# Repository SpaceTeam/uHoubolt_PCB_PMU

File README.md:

# µHoubolt Power Management Unit (PMU) Hardware

## Features
- Altimeter capability (barometer, IMU, 2x Low Side Fet)
- 2x Low Side Fet for camera
- 1x Optocoupler for payload enable
- 2x LiIon Charger
- Flash for data logging
- 2x CAN FD

## Known Issues
- CAN Rx and Tx are swapped on CAN1 and CAN2
- No Battery Voltage Sense
- No Pyro Voltage Sense
- Same Connector for 12V and 24V
- No direct hardware arming for primary altimax
- Supply Current Sense is connected to the wrong pin
- Layout: Battery connector is hard to disconnect because it's next to the mounting hole (threaded rod)
- When powering cameras from pyro voltage, their initial current draw is large enough to trigger the overcurrent protection --> all supplied devices might get power cycled when safety pin is pulled (especially bad for ECU, might cause igniters to fire, see ECU known issues)

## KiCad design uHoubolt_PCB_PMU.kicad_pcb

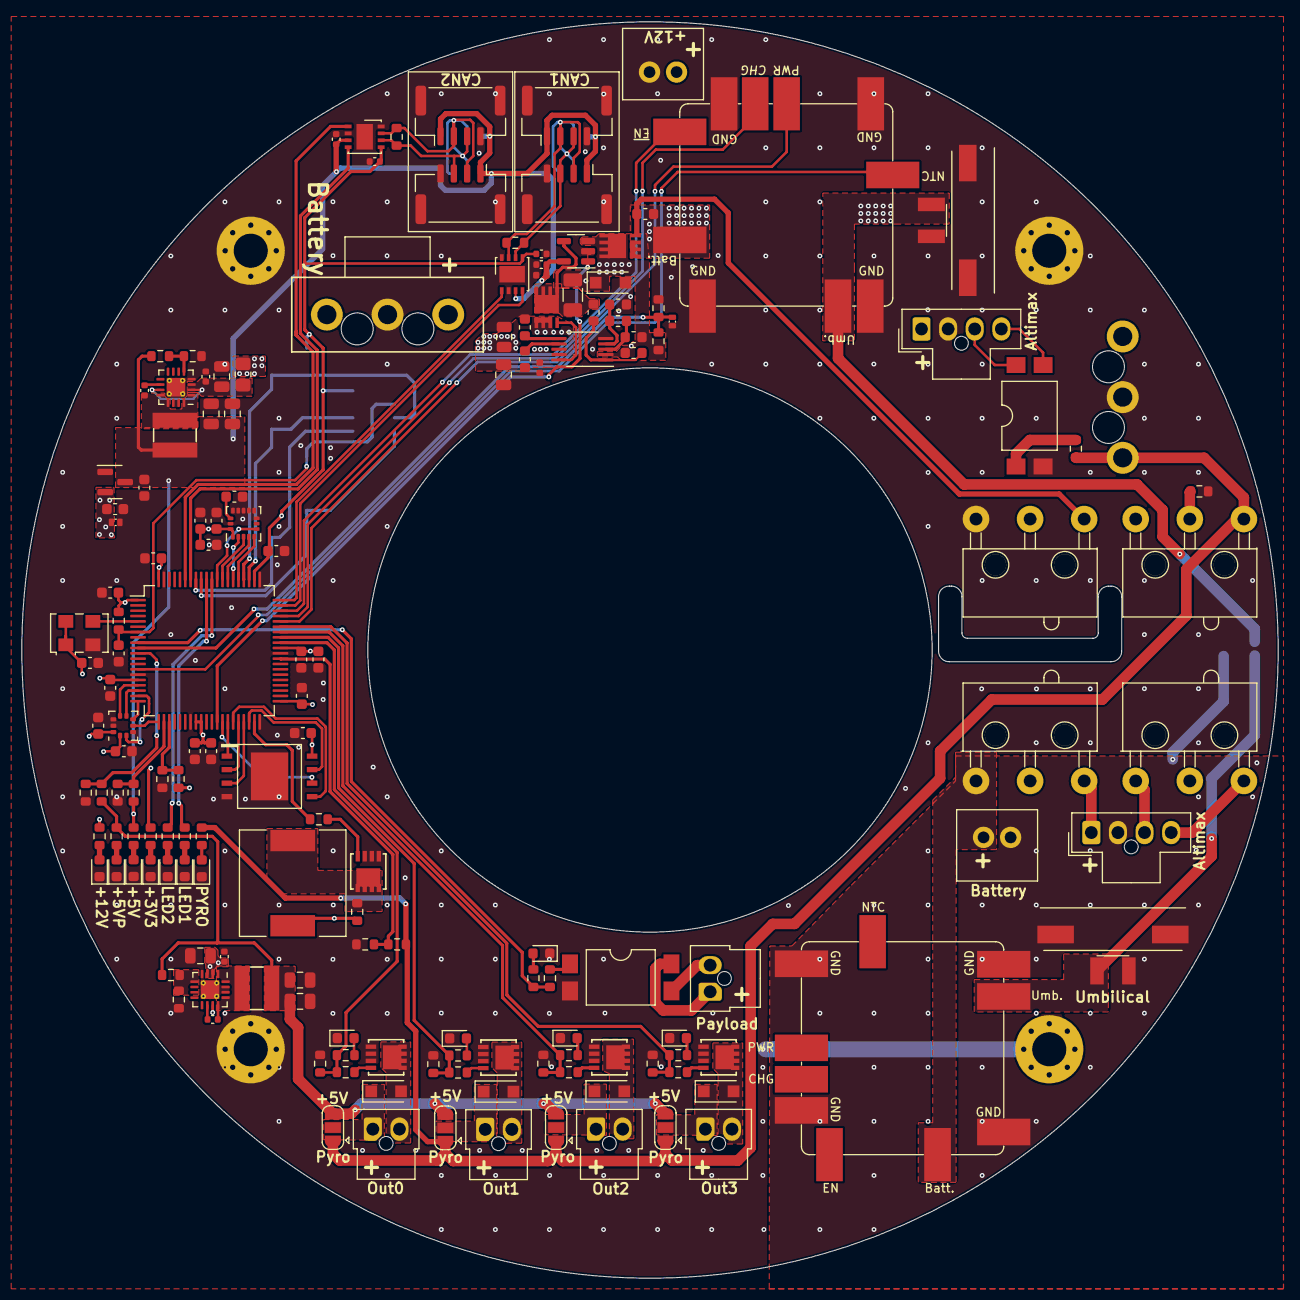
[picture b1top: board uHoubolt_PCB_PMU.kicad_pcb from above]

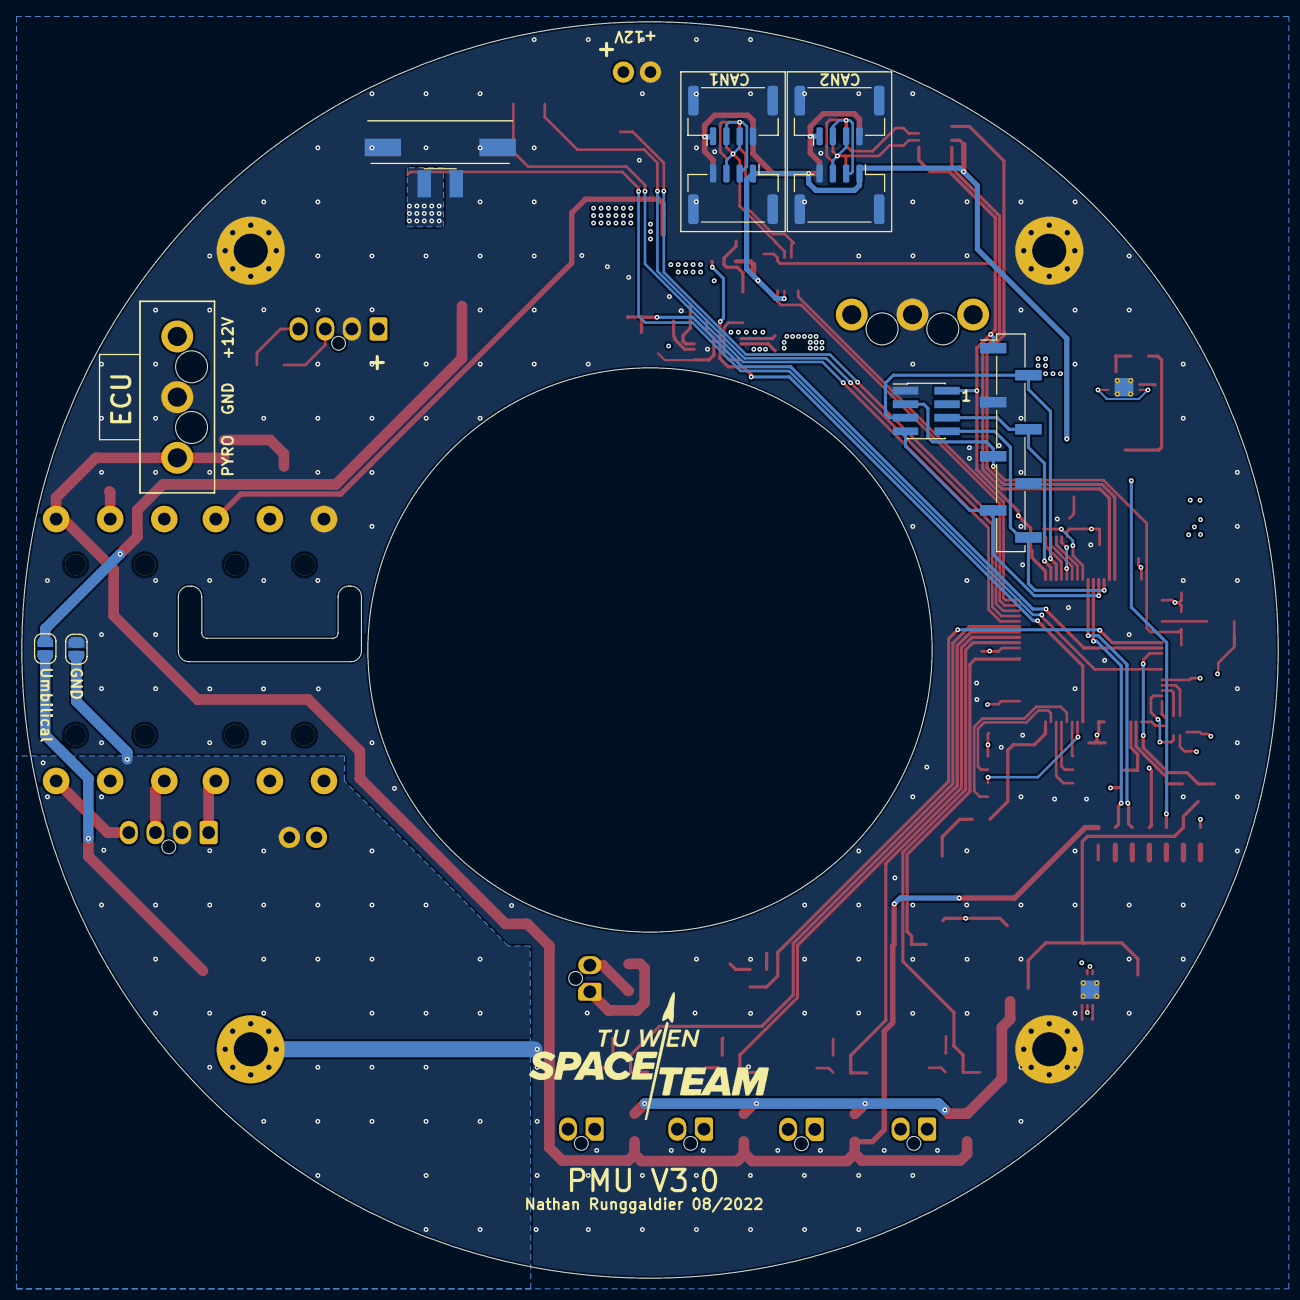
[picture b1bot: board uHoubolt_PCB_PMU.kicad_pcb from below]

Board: 4 copper layers, 118.0 x 118.0 mm, 174 parts (11 on the bottom side), 112 nets.

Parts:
C1: 470n; C_0603_1608Metric
C2, C20, C21, C23, C25, C26, C27, C28, C29, C30, C35, C40, C41, C42: 100n; C_0603_1608Metric
C3, C6, C15, C19, C32, C33, C37, C38, C45, C46: 100n; C_0402_1005Metric
C4, C5, C16, C17, C43, C44, C47, C48: 22u; C_0805_2012Metric
C22, C24, C31, C34, C36: 2u2; C_0603_1608Metric
C39: 10n; C_0603_1608Metric
D1: 30V; D_SOD-123F
D2: VIN; LED_0603_1608Metric
D3: Pyro; LED_0603_1608Metric
D4, D8: TVS 3V3; SOD882D
D7, D16: 5V; LED_0603_1608Metric
D9: 3V3; LED_0603_1608Metric
D10, D12, D14, D17: OUT; LED_0603_1608Metric
D11, D13, D15, D18: Shottky; D_SOD-123F
D25: Payload; LED_0603_1608Metric
F1: Fuse_Small; R_0805_2012Metric_Pad1.20x1.40mm_HandSolder
G1: SpaceTeam_LOGO; ST_Logo_new
H1, H2, H3, H4: M3; MountingHole_3.2mm_M3_Pad_Via
J1, J7: Conn_01x04; Molex_Nano-Fit_105309-xx04_1x04_P2.50mm_Vertical
J2: Battery; Molex_MegaFit_1x03_Vertical
J3: Power; Molex_MegaFit_1x03_Vertical
J4: BatteryAltimax; Molex_SL_1x2_Vertical
J5: Umbilical1; Molex_MicroFit_2Pin_Vertical
J9: Debug; PinHeader_1x08_P2.54mm_Vertical_SMD_Pin1Left
J10: Debug; PinHeader_2x04_P1.27mm_Vertical_SMD
J12, J14, J16, J18: CAN1; JST_GH_BM04B-GHS-TBT_1x04-1MP_P1.25mm_Vertical
J13, J15, J17, J19: CAN2; JST_GH_BM04B-GHS-TBT_1x04-1MP_P1.25mm_Vertical
J20, J21, J22, J24: Output; Molex_Nano-Fit_105309-xx02_1x02_P2.50mm_Vertical
J23: Payload; Molex_Nano-Fit_105309-xx02_1x02_P2.50mm_Vertical
J25: RCU; Molex_SL_1x2_Vertical
J27, J28: Umbilical0; Molex_MicroFit_2Pin_Vertical
JP2, JP3: Jumper_2_Open; SolderJumper-2_P1.3mm_Open_RoundedPad1.0x1.5mm
JP4, JP5, JP6, JP7: Jumper_3_Open; SolderJumper-3_P1.3mm_Open_RoundedPad1.0x1.5mm
L1, L3: 4.7u; SRN4018TA-4R7M
LED1, LED2: LED_Small_Filled; LED_0603_1608Metric
LS1: Speaker; Piezo_Buzzer
Q1: BSZ0905PNSATMA1; PG_TSDSON-8
Q2: BSZ0902NSATMA1; PG_TSDSON-8
Q3, Q4, Q5, Q6, Q7: SISA88DN or similar; PowerPAK_1212-8
R1, R8, R14, R20, R21, R25, R26, R33, R36, R39, R41, R46, R47, R48: 10k; R_0603_1608Metric
R2, R3, R4, R17, R18, R22, R31, R43, R44: R; R_0603_1608Metric
R5: NP; R_0603_1608Metric
R6: 2m; R_1206_3216Metric
R7: 0R; R_0603_1608Metric
R9: 47k; R_0603_1608Metric
R10, R16, R19, R23, R45: 1k; R_0603_1608Metric
R11, R12, R15, R28, R29, R30, R32, R34, R35, R37, R38, R40, R42, R49, R56: 120; R_0603_1608Metric
R13, R24, R27: 56k; R_0603_1608Metric
SW1: Power_1; D2F_A
SW2: Power_2; D2F_A1
SW3: Pyro_1; D2F_A
SW4: Pyro_2; D2F_A1
U1: LM5069; VSSOP-10_3x3mm_P0.5mm
U2: LMP8640 F; SOT-23-5
U3, U13: TS30041; QFN-16-1EP_3x3mm_P0.5mm_EP1.75x1.75mm_ThermalVias
U4, U14: LiIon_Charger; LiIon_Charger_Footprint
U5: STM32G491MET6-LQFP80; LQFP-80_12x12mm_P0.5mm
U6: W25Q256JV; WSON-8-8x6mm
U7: MCP1700-3302E; SOT-23
U8, U9: MCP2562FDx-x_MF; DFN-8-1EP_3x3mm_P0.65mm_EP1.55x2.4mm
U10: ICM-20602; LGA-16_3x3mm_P0.5mm_LayoutBorder3x5y
U11: LPS25HB; ST_HLGA-10_2.5x2.5mm_P0.6mm_LayoutBorder3x2y
U12, U15: SFH617A-1X007T; SMDIP-4_W9.53mm_Clearance8mm
X1: TXC-7C; Oscillator_SMD_TXC_7C-4Pin_5.0x3.2mm

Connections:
+3V3: C2.1, C21.2, C22.2, C23.2, C24.2, C25.2, C26.2, C27.1, C28.2, C29.2, C30.2, C32.1, C33.1, C34.2, C35.2, C36.1, C39.1, C41.2, C42.1, D8.1 (K), J9.1, J10.2, R8.1, R30.1, U5.1 (VBAT), U5.16 (VDD), U5.28 (VREF+), U5.29 (VDDA), U5.41 (VDD), U5.51 (VDD), U5.62 (VDD), U5.80 (VDD), U6.8 (VCC), U7.2 (VO), U8.5 (Vio), U9.5 (Vio), U10.1 (VDDIO), U10.16 (VDD), U11.1 (VDDio), U11.10 (VDD), X1.1 (EN), X1.4 (Vdd)
+5V: C19.1, C31.1, C37.1, C38.1, C47.2, C48.2, J12.1, J13.1, J14.1, J15.1, J16.1, J17.1, J18.1, J19.1, L3.2, R43.2, R45.1, R46.1, U2.5 (V+), U7.3 (VI), U8.3 (VDD), U9.3 (VDD)
+5VP: C16.2, C17.2, JP4.3 (B), JP5.3 (B), JP6.3 (B), JP7.3 (B), L1.2, R17.2, R19.1, R20.1
+12V: C3.1, C4.1, C5.2, C6.1, C43.1, J3.1, J7.1, J25.1, LS1.1, Q2.1 (S), R10.1, R13.1, R16.1, SW3.1 (A), U1.9 (OUT), U3.2 (VCC), U3.3 (VCC), U3.11 (VCC)
+BATT: J2.1, Q1.1 (S), R1.1, U4.2 (Battery)
/5V/Input: C44.2, C45.1, F1.2, U13.2 (VCC), U13.3 (VCC), U13.11 (VCC)
/5VP_Sense: R20.2, R21.1, U5.11 (PC3)
/5V_Sense: R46.2, R47.1, U5.22 (PC4)
/12V_Sense: R13.2, R14.1, U5.23 (PC5)
/BARO_INT: U5.17 (PA3), U11.7 (INT_DRDY)
/BARO_SPI1_MISO: U5.20 (PA6), U11.5 (SA0/MISO)
/BARO_SPI1_MOSI: U5.21 (PA7), U11.4 (SDA/MOSI)
/BARO_SPI1_NSS: U5.18 (PA4), U11.6 (~CS)
/BARO_SPI1_SCK: U5.19 (PA5), U11.2 (SCL/SCLK)
/Battery_Sense: D4.1 (K), R26.1, R27.2, U5.10 (PC2)
/CAN1_H: J12.2, J14.2, J16.2, J18.2, R28.1, U8.7 (CANH)
/CAN1_L: J12.3, J14.3, J16.3, J18.3, R28.2, U8.6 (CANL)
/CAN1_RX: U5.59 (PA11), U8.4 (RXD)
/CAN1_TX: U5.60 (PA12), U8.1 (TXD)
/CAN2_H: J13.2, J15.2, J17.2, J19.2, R29.1, U9.7 (CANH)
/CAN2_L: J13.3, J15.3, J17.3, J19.3, R29.2, U9.6 (CANL)
/CAN2_RX: U5.74 (PB5), U9.4 (RXD)
/CAN2_TX: U5.75 (PB6), U9.1 (TXD)
/GND_Altimax: J1.2, J4.2, J5.2, J5.MP (MountPin), JP3.2 (B), U14.1 (GND), U14.4 (GND), U14.7 (GND), U14.9 (GND)
/HSE_CLK: U5.5 (PF0-OSC_IN), X1.3 (OUT)
/IMU_INT: U5.69 (PD0), U10.6 (INT)
/IMU_NSS: U5.65 (PA15), U10.5 (~CS)
/IMU_SPI3_MISO: U5.67 (PC11), U10.4 (SAO/SD0)
/IMU_SPI3_MOSI: U5.68 (PC12), U10.3 (SDA/SDI)
/IMU_SPI3_SCK: U5.66 (PC10), U10.2 (SCL/SPC)
/LED1: R11.1, U5.71 (PD2)
/LED2: R12.1, U5.70 (PD1)
/NRST: C20.1, J9.5, J10.3, R8.2, U5.7 (PG10-NRST)
/NTC: U4.8 (NTC), U5.14 (PA2)
/Out0: R32.1, R33.2, R34.1, U5.52 (PC6)
/Out1: R35.1, R36.2, R37.1, U5.53 (PC7)
/Out2: R38.1, R39.2, R40.1, U5.54 (PC8)
/Out3: R42.1, R48.2, R49.1, U5.55 (PC9)
/Payload: R31.1, R56.1, U5.9 (PC1)
/Pyro_Sense: R24.2, R25.1, U5.49 (PD10)
/QSPI1_BK1_IO0: U5.35 (PE12), U6.5 (DI(IO0))
/QSPI1_BK1_IO1: U5.36 (PE13), U6.2 (DO(IO1))
/QSPI1_BK1_IO2: U5.37 (PE14), U6.3 (~WP(IO2))
/QSPI1_BK1_IO3: U5.38 (PE15), U6.7 (~RESET(IO3))
/QSPI1_BK1_NCS: U5.34 (PE11), U6.1 (~CS)
/QSPI1_CLK: U5.33 (PE10), U6.6 (CLK)
/SUPPLY_CURRENT_SENSE: U2.1, U5.32 (PE9)
/SWCLK: J9.2, J10.5, U5.64 (PA14)
/SWDIO: J9.4, J10.6, U5.63 (PA13)
/Speaker: R15.1, U5.39 (PB10)
/UART_RX: J9.8, J10.8, U5.73 (PB4)
/UART_TX: J9.7, J10.7, U5.72 (PB3)
/Vcharge: J27.1, J28.1, JP2.1 (A), U4.10 (Umb.)
/Vcharge1: J5.1, JP2.2 (B), U14.10 (Umb.)
/Vin: D1.1 (A1), F1.1, Q1.3 (D), R2.1, R5.1, R6.1, R27.1, U1.2 (VIN), U2.3 (+)
/~ACOK: U4.6 (ACOK), U5.56 (PA8)
/~CHGOK: U4.5 (CHGOK), U5.57 (PA9)
/~EN: U4.3 (EN), U5.58 (PA10)
GND: C1.2, C2.2, C3.2, C4.2, C5.1, C6.2, C16.1, C17.1, C19.2, C20.2, C21.1, C22.1, C23.1, C24.1, C25.1, C26.1, C27.2, C28.1, C29.1, C30.1, C31.2, C32.2, C33.2, C34.1, C35.1, C36.2, C37.2, C38.2, C39.2, C40.2, C41.1, C42.2, C43.2, C44.1, C45.2, C47.1, C48.1, D1.2 (A2), D2.1 (K), D3.1 (K), D4.2 (A), D7.1 (K), D8.2 (A), D9.1 (K), D10.1 (K), D12.1 (K), D14.1 (K), D16.1 (K), D17.1 (K), D25.1 (K), H1.1, H2.1, H3.1, H4.1, J2.2, J3.2, J7.2, J9.3, J10.1, J12.4, J12.MP (MountPin), J13.4, J13.MP (MountPin), J14.4, J14.MP (MountPin), J15.4, J15.MP (MountPin), J16.4, J16.MP (MountPin), J17.4, J17.MP (MountPin), J18.4, J18.MP (MountPin), J19.4, J19.MP (MountPin), J25.2, J27.2, J27.MP (MountPin), J28.2, J28.MP (MountPin), JP3.1 (A), LED1.1 (K), LED2.1 (K), Q3.3 (S), Q4.3 (S), Q5.3 (S), Q6.3 (S), Q7.3 (S), R4.2, R9.2, R14.2, R18.2, R21.2, R25.2, R26.2, R33.1, R36.1, R39.1, R41.2, R44.2, R47.2, R48.1, SW1.1 (A), U1.5 (GND), U2.2 (GND), U3.4 (GND), U3.14 (PGND), U3.15 (PGND), U3.17 (PAD), U4.1 (GND), U4.4 (GND), U4.7 (GND), U4.9 (GND), U5.15 (VSS), U5.27 (VSSA), U5.40 (VSS), U5.50 (VSS), U5.61 (VSS), U5.79 (VSS), U6.4 (GND), U6.9 (PAD), U7.1 (GND), U8.2 (VSS), U8.8 (STBY), U8.9 (PAD), U9.2 (VSS), U9.8 (STBY), U9.9 (PAD), U10.8 (FSYNC), U10.9 (GND), U10.10 (GND), U10.11 (GND), U10.12 (GND), U10.13 (GND), U10.15 (GND), U11.3 (GND), U11.8 (GND), U11.9 (GND), U12.2, U13.4 (GND), U13.14 (PGND), U13.15 (PGND), U13.17 (PAD), U15.2, X1.2 (GND)
unnamed: C1.1, U1.6 (TIMER)
unnamed: C15.1, L1.1, U3.1 (VSW), U3.12 (VSW), U3.13 (VSW), U3.16 (VSW)
unnamed: C15.2, U3.10 (BST)
unnamed: C40.1, U10.14 (REGOUT)
unnamed: C46.1, L3.1, U13.1 (VSW), U13.12 (VSW), U13.13 (VSW), U13.16 (VSW)
unnamed: C46.2, U13.10 (BST)
unnamed: D2.2 (A), R10.2
unnamed: D3.2 (A), R23.2
unnamed: D7.2 (A), R19.2
unnamed: D9.2 (A), R30.2
unnamed: D10.2 (A), R32.2
unnamed: D11.1 (K), J20.1, JP4.2 (C)
unnamed: D11.2 (A), J20.2, Q4.2 (D)
unnamed: D12.2 (A), R35.2
unnamed: D13.1 (K), J21.1, JP5.2 (C)
unnamed: D13.2 (A), J21.2, Q5.2 (D)
unnamed: D14.2 (A), R38.2
unnamed: D15.1 (K), J22.1, JP6.2 (C)
unnamed: D15.2 (A), J22.2, Q6.2 (D)
unnamed: D16.2 (A), R45.2
unnamed: D17.2 (A), R42.2
unnamed: D18.1 (K), J24.1, JP7.2 (C)
unnamed: D18.2 (A), J24.2, Q7.2 (D)
unnamed: D25.2 (A), R56.2
unnamed: J1.1, SW2.2 (B)
unnamed: J1.3, SW4.1 (A)
unnamed: J1.4, SW4.2 (B)
unnamed: J4.1, SW2.1 (A), U14.2 (Battery)
unnamed: J7.3, U15.4
unnamed: J7.4, U15.3
unnamed: J23.1, U12.4
unnamed: J23.2, U12.3
unnamed: LED1.2 (A), R11.2
unnamed: LED2.2 (A), R12.2
unnamed: LS1.2, Q3.2 (D), R16.2
unnamed: Q1.2 (G), R1.2, SW1.2 (B)
unnamed: Q2.2 (G), U1.10 (GATE)
unnamed: Q2.3 (D), R6.2, R7.2, U2.4 (-)
unnamed: Q3.1 (G), R15.2
unnamed: Q4.1 (G), R34.2
unnamed: Q5.1 (G), R37.2
unnamed: Q6.1 (G), R40.2
unnamed: Q7.1 (G), R49.2
unnamed: R2.2, R3.1, U1.3 (UVLO)
unnamed: R3.2, R4.1, U1.4 (OVLO)
unnamed: R5.2, R7.1, U1.1 (SENSE)
unnamed: R9.1, U1.7 (PWR)
unnamed: R17.1, R18.1, U3.5 (FB)
unnamed: R22.2, U15.1
unnamed: R31.2, U12.1
unnamed: R41.1, SW3.3 (C)
unnamed: R43.1, R44.1, U13.5 (FB)
PYRO: J3.3, JP4.1 (A), JP5.1 (A), JP6.1 (A), JP7.1 (A), R22.1, R23.1, R24.1, SW3.2 (B)

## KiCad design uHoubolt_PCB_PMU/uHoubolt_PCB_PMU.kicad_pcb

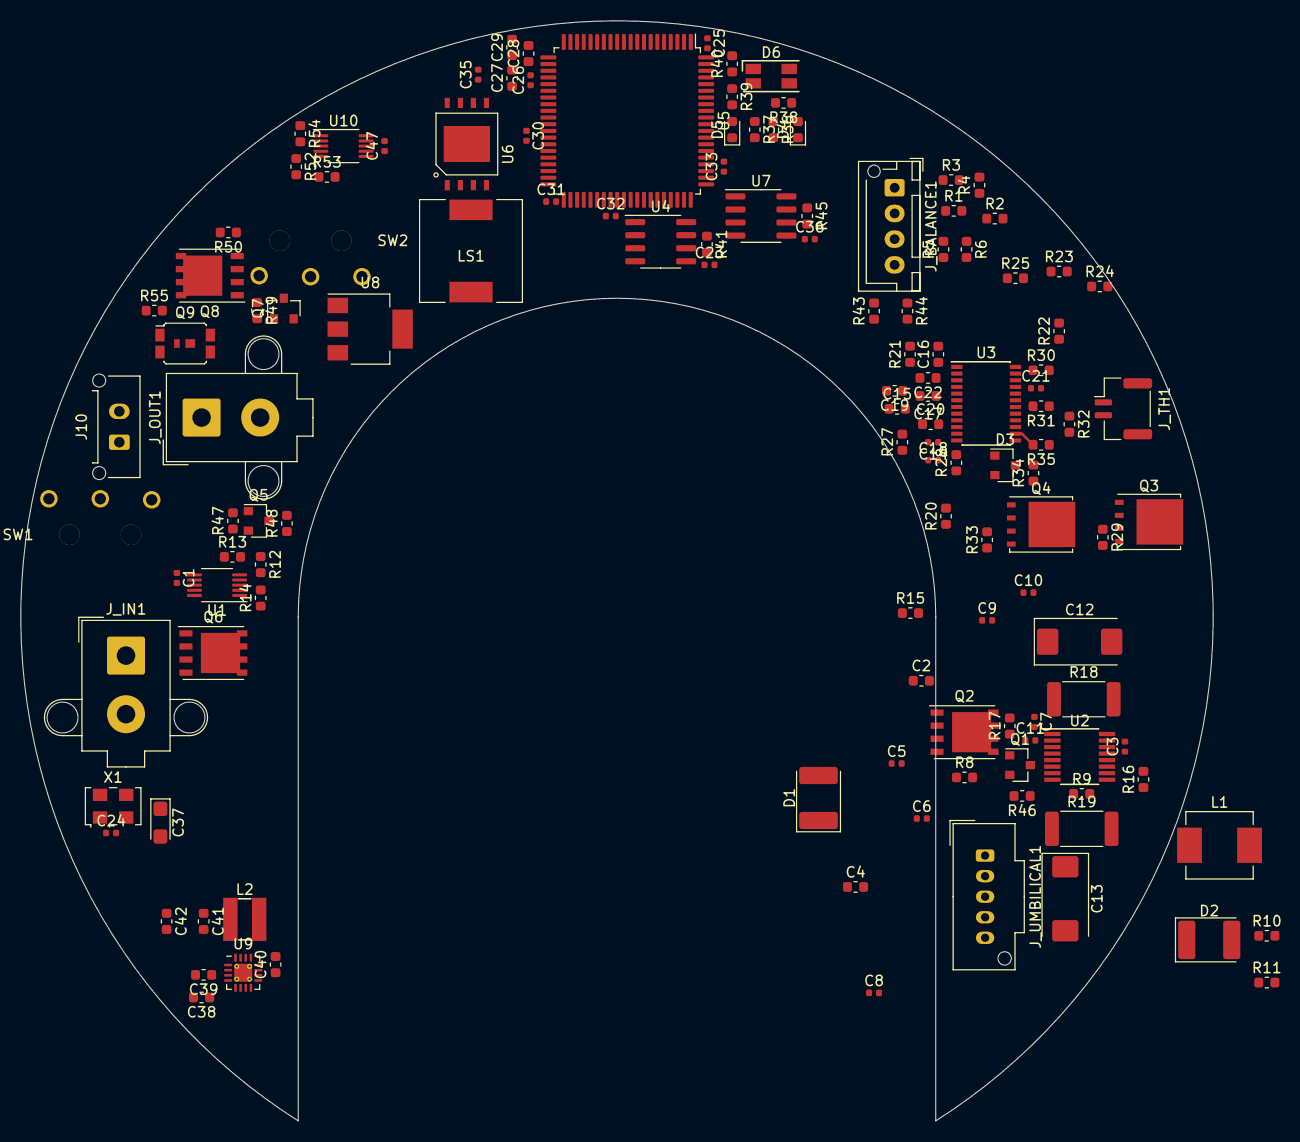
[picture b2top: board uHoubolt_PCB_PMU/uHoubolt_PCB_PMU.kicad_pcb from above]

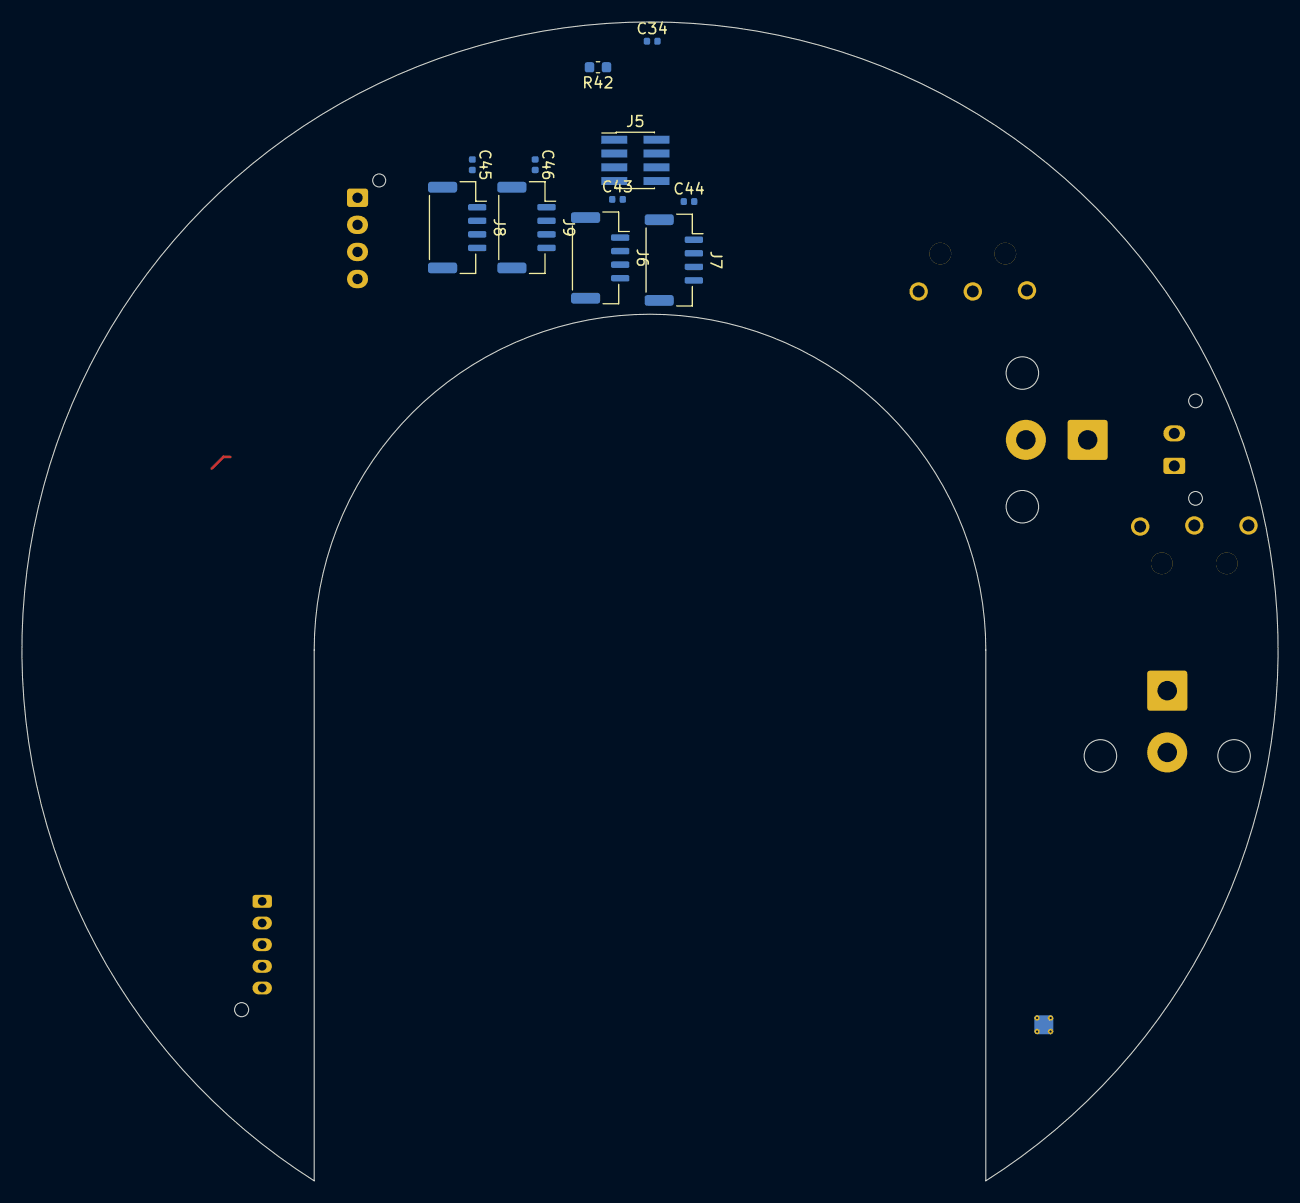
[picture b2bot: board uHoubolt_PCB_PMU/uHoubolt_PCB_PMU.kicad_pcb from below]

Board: 4 copper layers, 116.0 x 107.0 mm, 141 parts (11 on the bottom side), 100 nets.

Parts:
C1, C10, C14, C18, C21, C23, C24, C25, C30, C31, C32, C33, C34, C35, C36, C43, C44, C45, C46, C47: 100n; C_0402_1005Metric
C2, C15, C16, C17, C19, C20, C22, C27, C28, C29: 1u; C_0603_1608Metric
C3, C5: 220n; C_0402_1005Metric
C4: 2.2u; C_0603_1608Metric
C6: 1n; C_0402_1005Metric
C7, C11, C26: 10n; C_0402_1005Metric
C8, C9: 47n; C_0402_1005Metric
C12: 47u; CP_EIA-7343-43_Kemet-X
C13: 68uF; CP_EIA-7343-31_Kemet-D
C37: 22u; CP_EIA-3216-18_Kemet-A
C38: 10µ; C_0603_1608Metric
C39, C40: 100n; C_0603_1608Metric
C41, C42: 22µ; C_0603_1608Metric
D1, D2: D_Schottky; D_2114_3652Metric
D3: D_Zener; D_SOT-23_ANK
D4, D5: LED; LED_0603_1608Metric
D6: LED_RGBC; LED_RGB_1210
J5: Conn_02x04_Odd_Even; PinHeader_2x04_P1.27mm_Vertical_SMD
J6, J7, J8, J9: Conn_01x04_MountingPin; JST_GH_SM04B-GHS-TB_1x04-1MP_P1.25mm_Horizontal
J10: Conn_01x02; Molex_Micro-Fit_3.0_43650-0215_1x02_P3.00mm_Vertical
J_BALANCE1: Conn_01x04; JST_XH_B4B-XH-AM_1x04_P2.50mm_Vertical
J_IN1: Conn_01x02; Molex_Mega-Fit_76829-0002_2x01_P5.70mm_Vertical
J_OUT1: Conn_01x02; Molex_Mega-Fit_76829-0002_2x01_P5.70mm_Vertical
J_TH1: Conn_01x02_MP; JST_GH_BM02B-GHS-TBT_1x02-1MP_P1.25mm_Vertical
J_UMBILICAL1: Conn_01x04_MountingPin; Molex_MicroClasp_55932-0510_1x05_P2.00mm_Vertical
L1: 10uH; L_Vishay_IHLP-2525
L2: 4µ7; SRN4018TA-4R7M
LS1: Speaker_Crystal; Piezo_Buzzer
Q1: ZXMN3F30FH; SOT-23
Q2, Q6, Q8: Si7141DP; PowerPAK_SO-8_Single
Q3, Q4: CSD17303Q5; TDSON-8-1
Q5, Q7: MMBT3904; SOT-23
Q9: BSF030NE2LQ; DirectFET_SQ
R1: 3k; R_0603_1608Metric
R2: 1k5; R_0603_1608Metric
R3: 500; R_0603_1608Metric
R4, R6, R21, R47, R48, R49, R50, R55: 1k; R_0603_1608Metric
R5, R15, R30, R31, R42, R43, R46: 10k; R_0603_1608Metric
R8: 200; R_0603_1608Metric
R9, R10, R11, R32: 100k; R_0603_1608Metric
R12, R13, R14, R52, R53, R54: 2.7k; R_0603_1608Metric
R16, R17: 4.7; R_0603_1608Metric
R18: 0.033; R_2512_6332Metric
R19: 0.068; R_2512_6332Metric
R20, R22, R23, R24: 134; R_0603_1608Metric
R25, R27: 100; R_0603_1608Metric
R28: 4.5k; R_0603_1608Metric
R29, R33: 1M; R_0603_1608Metric
R34: 3.3M; R_0603_1608Metric
R35: 470k; R_0603_1608Metric
R36, R37, R38, R39, R40, R41, R45: 120; R_0603_1608Metric
R44: 2k; R_0603_1608Metric
SW1, SW2: SW_Push_SPDT; MicroSwitch
U1, U10: INA226; VSSOP-10_3x3mm_P0.5mm
U2: MAX1873SEEE; QSOP-16_3.9x4.9mm_P0.635mm
U3: BQ77915; TSSOP-24_4.4x7.8mm_P0.65mm
U4, U7: MCP2562FDT-H_SN; SOIC-8_3.9x4.9mm_P1.27mm
U5: STM32G491MET6-LQFP80; LQFP-80_14x14mm_P0.65mm
U6: W25Q256JV; WSON-8-8x6mm
U8: MCP1826S; SOT-223-3_TabPin2
U9: TS30041-M050QFNR; QFN-16-1EP_3x3mm_P0.5mm_EP1.75x1.75mm_ThermalVias
X1: TXC-7C; Oscillator_SMD_TXC_7C-4Pin_5.0x3.2mm

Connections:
+3V3: C1.1, C23.1, C24.1, C25.1, C26.2, C27.2, C28.2, C29.2, C30.2, C31.2, C32.2, C33.2, C34.2, C35.1, C36.1, C37.2, C47.1, J5.2, R12.1, R13.1, R14.1, R42.2, R52.1, R53.1, R54.1, U1.6, U4.5, U5.16, U5.41, U5.51, U5.62, U5.80, U6.8, U7.5, U8.3, U10.1, U10.6, X1.1, X1.4
+5V: C41.1, C42.1, C43.2, C44.2, C45.2, C46.2, J6.1, J7.1, J8.1, J9.1, L2.2, U4.3, U7.3, U8.1, U9.5
+BATT: C38.1, C39.1, J_OUT1.1, Q8.1, Q8.2, Q8.3, R43.1, R50.2, SW2.1, U1.9, U9.2, U9.3, U9.11
/ALERT: R14.2, R54.2, U1.3, U5.12, U10.3
/BATT3V6: J_BALANCE1.2, R3.1, R22.2
/BATT7V2: J_BALANCE1.3, R1.1, R20.2
/BATT_GND: C14.2, C16.2, C19.2, C20.1, C21.2, C22.2, J_BALANCE1.1, J_IN1.1, J_TH1.2, J_TH1.MP, R23.2, R25.2, R32.1, U3.9, U3.16, U3.20, U3.23, U3.24
/BATT_VCC: C13.1, J_BALANCE1.4, J_IN1.2, Q6.1, Q6.2, Q6.3, R19.1, R21.2, R24.2, R48.2, SW1.1, U2.10
/CAN_H: J6.2, J7.2, J_UMBILICAL1.2, R41.1, U4.7
/CAN_L: J6.3, J7.3, J_UMBILICAL1.3, R41.2, U4.6
/CELL_3V6: R3.2, R4.1, U5.45
/CELL_7V2: R1.2, R2.1, U5.44
/CHARGE_VOLT: R5.2, R6.1, U5.43
/DISABLE: R8.2, U5.13
/IOUT: U2.7, U5.31
/MCU/Buzzer_1: LS1.1, U5.55
/MCU/Buzzer_2: LS1.2, U5.54
/MCU/CAN1_RX: U4.4, U5.69
/MCU/CAN1_TX: U4.1, U5.70
/MCU/CAN2_H: J8.2, J9.2, R45.1, U7.7
/MCU/CAN2_L: J8.3, J9.3, R45.2, U7.6
/MCU/CAN2_RX: U5.74, U7.4
/MCU/CAN2_TX: U5.75, U7.1
/MCU/CLK: U5.5, X1.3
/MCU/LED_1: R36.2, U5.68
/MCU/LED_2: R37.2, U5.71
/MCU/LED_B: R38.2, U5.73
/MCU/LED_G: R39.2, U5.76
/MCU/LED_R: R40.2, U5.78
/MCU/NRST: J5.3, R42.1, U5.7
/MCU/PD10: R43.2, R44.1, U5.49
/MCU/PE7: U5.30, U9.8
/MCU/QSPI1_BK1_IO0: U5.35, U6.5
/MCU/QSPI1_BK1_IO1: U5.36, U6.2
/MCU/QSPI1_BK1_IO2: U5.37, U6.3
/MCU/QSPI1_BK1_IO3: U5.38, U6.7
/MCU/QSPI1_BK1_NC: U5.34, U6.1
/MCU/QSPI1_CLK: U5.33, U6.6
/MCU/SWCLK: J5.5, U5.64
/MCU/SWDIO: J5.6, U5.63
/MCU/UART4_RX: J5.8, U5.67
/MCU/UART4_TX: J5.7, U5.66
/SCL: R13.2, R53.2, U1.5, U5.56, U10.5
/SDA: R12.2, R52.2, U1.4, U5.57, U10.4
GND: C1.2, C2.1, C4.2, C5.1, C6.1, C7.1, C8.1, C9.1, C10.1, C11.1, C12.2, C13.2, C23.2, C24.2, C25.2, C26.1, C27.1, C28.1, C29.1, C30.1, C31.1, C32.1, C33.1, C34.1, C35.2, C36.2, C37.1, C38.2, C39.2, C41.2, C42.2, C43.1, C44.1, C45.1, C46.1, C47.2, D2.2, D4.1, D5.1, D6.4, J5.1, J6.4, J6.MP, J7.4, J7.MP, J8.4, J8.MP, J9.4, J9.MP, J_OUT1.2, J_UMBILICAL1.4, Q1.2, Q4.5, Q5.2, Q7.2, Q9.3, R2.2, R4.2, R6.2, R11.2, R34.1, R35.1, R44.2, R46.2, R55.2, U1.1, U1.2, U1.7, U2.12, U4.2, U4.8, U5.15, U5.27, U5.40, U5.50, U5.61, U5.79, U6.4, U7.2, U7.8, U8.2, U9.4, U9.14, U9.15, U9.17, U10.2, U10.7, X1.2
unnamed: C2.2, R9.2, R10.1, U2.9
unnamed: C3.1, U2.13
unnamed: C3.2, C5.2, D1.1, R16.2, R18.1, U2.15
unnamed: C4.1, U2.16
unnamed: C6.2, R15.2, U2.4
unnamed: C7.2, R17.1, U2.1
unnamed: C8.2, U2.5
unnamed: C9.2, U2.3
unnamed: C10.2, R15.1
unnamed: C11.2, R16.1, U2.2
unnamed: C12.1, Q2.1, Q2.2, Q2.3, R17.2, R18.2
unnamed: C14.1, C18.1, R25.1, U3.10
unnamed: C15.1, C17.2, R20.1, U3.6
unnamed: C15.2, C19.1, R22.1, U3.7
unnamed: C16.1, R21.1, R30.2, U3.1
unnamed: C17.1, R24.1, U3.3, U3.4, U3.5
unnamed: C18.2, C21.1, R27.1, U3.11
unnamed: C20.2, R23.1, U3.8
unnamed: C22.1, U3.2
unnamed: C40.1, U9.10
unnamed: C40.2, L2.1, U9.1, U9.12, U9.13, U9.16
unnamed: D2.1, L1.1, Q2.5
unnamed: D3.1, Q4.4, R33.1, R34.2
unnamed: D3.2, R33.2, U3.13
unnamed: D4.2, R36.1
unnamed: D5.2, R37.1
unnamed: D6.1, R40.1
unnamed: D6.2, R39.1
unnamed: D6.3, R38.1
unnamed: J10.1, Q9.1
unnamed: J10.2, U10.9
unnamed: J_TH1.1, R31.1, U3.18
unnamed: L1.2, R19.2, U2.11
unnamed: Q1.1, R8.1, R46.1
unnamed: Q1.3, R9.1, U2.6
unnamed: Q2.4, U2.14
unnamed: Q3.1, Q3.2, Q3.3, R27.2, R29.1
unnamed: Q3.4, R28.1, R29.2
unnamed: Q3.5, Q4.1, Q4.2, Q4.3
unnamed: Q5.1, R47.2
unnamed: Q5.3, Q6.4, R48.1
unnamed: Q6.5, U1.8, U1.10
unnamed: Q7.1, R49.2
unnamed: Q7.3, Q8.4, R50.1
unnamed: Q8.5, U10.8, U10.10
unnamed: Q9.2, R55.1
unnamed: R10.2, R11.1, U2.8
unnamed: R28.2, U3.12
unnamed: R30.1, U3.22
unnamed: R31.2, U3.19
unnamed: R32.2, U3.17
unnamed: R35.2, U3.14
unnamed: R47.1, SW1.2
unnamed: R49.1, SW2.2
VCC: D1.2, J_UMBILICAL1.1, R5.1

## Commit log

2020-11-16 add submodule
2020-11-16 create kicad project with library paths
2020-11-17 fix library path
2020-11-19 update TXV_LIB
2020-12-03 add mcu
2020-12-17 balancer connected
2020-12-21 charge controller added
2020-12-24 hierarchies, buck converters added
2020-12-25 added CAN connector, current measurement and hierarchial labels
2021-01-03 add thermistor
2021-01-03 add current measurement
2021-01-03 add resistor values of regulator
2021-01-03 connect labels to muC
2021-01-03 change labels
2021-01-03 add metadata
2021-01-03 small fix balancer schematic
2021-01-03 replace mosfet
2021-01-03 change voltage divider values
2021-01-03 add voltage divider sys_load
2021-01-03 bat+ lable change, change mosfets balancer, remove sys_load
2021-01-04 Add descriptions
2021-01-04 change description
2021-01-05 update main
2021-01-05 Cleanup
2021-01-12 unify notation, connect NoConnects, revise balancer, add output connector
2021-01-12 add NoConnects, add capacitor footprints, add pulldown to Q1
2021-01-13 solve ERC errors
2021-01-17 connect power flags, update main
2021-04-07 add mosfet in schematic, draw outer bounds of pcb
2021-04-11 add ignition bus, placement 75% done
2021-04-18 add footprints of 2 shunts
2021-04-19 placing components 85% done
2021-05-13 new processor chip and add some suddenly missing footprints
2021-12-10 removed old project (moved to branch old)
2021-12-10 added new PMU project
2021-12-21 Added ECU to PMU
2021-12-21 Revert "Added ECU to PMU"
    This reverts commit 9e77d8288f64199274fc49822545c9b66851eb22.
2021-12-21 PMU ECU Combo (Fixed git mistakes)
2021-12-22 PMU Layout
2021-12-22 New Layout
2021-12-22 Release Version of PMU V1
2021-12-22 added new step file
2022-04-14 WIP PMU V2
2022-04-29 [WIP] Fixed References and Preps for PMUv2
2022-04-30 [WIP] PMUv2
2022-05-10 PMU v2 WIP
2022-05-11 PMU V2 "ready to order"?
2022-05-12 v2.0
2022-08-10 V3 Init Commit
    Fix of known issues of v2
2022-08-16 Schematic: Changed Polarity of umbilical connectors Schematic: Added TVS diode to battery_sense Schematic: Some minor prettyfication
    Still wrong: Main LiIon Charger Enable connect to STM32
2022-08-18 PMU V3 "ready to order?"
    ready to validate changes
2022-08-18 Revert "PMU V3 "ready to order?""
    This reverts commit e5aaef69110c3557dfda333950fee24891806424.
2022-08-18 PMU Ready for check
    Ready for conformity check
2022-08-19 V3 Updated ready for check
2022-08-19 V3 2. Update ready for check
2022-08-20 Update of v3
    Changed the silkscreen + more pads
2022-08-29 V3 ordered
2023-01-22 Add license
